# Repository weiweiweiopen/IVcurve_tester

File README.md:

# IVcurve_tester — Basic and Charging Boards

An I–V measurement circuit for dye-sensitized solar cells (DSSCs) and other low-power photovoltaic devices. Both boards use a **LOLIN S3 Mini, ADG706 load multiplexer, ADS1115 ADC, and Adafruit 4814 e-paper display**.

## Design Credits

- The basic board derives from **Marc Dusseiller's ([@dusjagr](https://github.com/dusjagr)) [IVcurve_tester](https://github.com/dusjagr/IVcurve_tester)**, including its original I–V measurement architecture, hardware, and code. This derivative adapts the carrier, GPIO assignments, and display interface.
- The charging board's **energy-harvesting, storage, power-control, and derivative PCB design was completed by Sol 6.1**.
- The original MIT copyright is retained in [LICENSE](LICENSE). Additional component-library attribution is provided in [NOTICE](NOTICE.md).

## Electrical Overview

| Function | Basic Board | Charging Board |
|---|---|---|
| System power | USB | DSSC harvesting and a controlled 5V boost supply; USB maintenance input |
| DUT connection | One DSSC, positive and negative collector pads at J1 | Same single-DSSC interface |
| I–V load selection | ADG706, 16 resistive loads | ADG706, 16 resistive loads |
| Voltage measurement | ADS1115 | ADS1115 |
| Energy harvesting | — | AEM10941 |
| Energy storage | — | Two parallel 1.5F / 5V supercapacitor packs, 3F total |
| Main power control | USB-powered operation | READY and timer logic, TPS61023 boost, TPS22917 load switch |
| Harvest/measurement switching | DUT connected to the measurement circuit | K1 relay switches the DSSC between harvesting and measurement |

## Basic Board

USB powers the MCU, ADC, and display. The DSSC is the device under test, rather than the MCU's power source.

The ADG706 selects one of 16 load resistors. The ADS1115 measures the voltage at each load point, and the firmware calculates current and power:

```text
I = V / Rpath
P = V × I
```

`Rpath` includes the selected resistor, multiplexer on-resistance, traces, and contacts. The supplied firmware uses nominal resistor values until measured path resistances and ADC calibration are entered. The ADS1115's ±4.096V gain setting describes its conversion scale; the input must still comply with its supply-dependent electrical limits.

The display interface uses the Adafruit 4814 SSD1680 panel at 250 × 122 pixels. Measurement starts from the button or the serial `SCAN` command. See the [basic firmware instructions](firmware/basic/README.md) for operation and GPIO assignments.

## Charging Board

The charging circuit harvests energy from the DSSC and stores it in **supercapacitors**. C201 and C202 are 1.5F / 5V PHB packs connected in parallel: the nominal total capacitance is **3F**, and the voltage rating remains **5V**.

```mermaid
flowchart TD
    DSSC[DSSC] --> K1[K1 relay]
    K1 -->|De-energized: harvest| AEM[AEM10941 harvester]
    AEM --> STORE[VSTORE: 3F supercapacitor bank]
    STORE --> AON[TPS7A02 always-on 3.3V]
    AON --> CONTROL[TPL5111 timer and READY logic]
    CONTROL -->|PM_READY AND TIMER_REQUEST| BOOST[TPS61023 5V boost]
    STORE --> BOOST
    BOOST --> SWITCH[TPS22917 controlled by JP201]
    SWITCH --> MCU[MCU, display, and measurement circuit]
    MCU -->|SCAN_MODE| K1
    K1 -->|Energized: measure| LOAD[ADG706 loads and ADS1115 sensing]
    MCU -->|MCU_DONE| CONTROL
```

### Harvesting and Storage

With K1 de-energized, the DSSC positive terminal connects to `HARV_P` and the AEM10941. The measurement load and ADC sensing branch are disconnected by the relay contacts.

The AEM10941 converts harvested energy into stored energy at `VSTORE`. Its configuration pins are set to `CFG=000`, corresponding to the schematic's nominal **70% Voc** MPPT setting. This hardware harvesting setting is separate from the MCU's I–V sweep and measured maximum-power-point calculation.

R280–R283 configure the AEM10941's charge and discharge thresholds. These thresholds govern when charging is limited, when stored energy is ready for use, and when the system should stop drawing from storage.

### Main Supply Control

TPS7A02 supplies the always-on 3.3V control domain. The main supply enable is:

```text
BOOST_EN = PM_READY AND TIMER_REQUEST
```

TPL5111 is configured for a nominal interval of approximately 600 seconds. The timer interval schedules a power request; actual operation also depends on the stored-energy condition. TPS61023 boosts `VSTORE` to `SOLAR_5V`, and TPS22917 connects that supply to the module's VBUS when enabled through JP201.

### Measurement and Return to Harvesting

The charging controller requires the following sequence:

1. Disable the ADG706 load before changing the relay state.
2. Assert `SCAN_MODE` to energize K1. The DSSC then connects to `LOAD_P`, while the second relay pole connects it to `SENSE_P` for the ADC. The harvesting branch is disconnected during the sweep.
3. Wait for relay contacts and the analog input to settle, then scan the load resistors and read the ADS1115.
4. Disable the load and release K1 to reconnect the DSSC to the harvester.
5. Complete the required logging/display operation and signal `MCU_DONE` through the Schmitt buffer to end the main-power interval.

`POWER_WARN_N` provides a storage-related warning input for early termination. Firmware must handle this input, relay settling, and DONE timing. The supplied basic USB firmware does not implement this autonomous charging-control sequence.

| Charging control signal | MCU GPIO | Function |
|---|---:|---|
| `SCAN_MODE` | 12 | Select harvesting or measurement through K1 |
| `MCU_DONE` | 13 | End the timer-controlled main-power interval |
| `POWER_WARN_N` | 11 | Storage/power warning input |

### USB Power and Energy Budget

Set **JP201 to OFF before connecting USB**. JP201 controls the TPS22917 load-switch path between the harvested 5V supply and module VBUS. USB is used as a maintenance supply with that path disabled.

For a supercapacitor bank, usable energy between two storage voltages is:

```text
Eusable = 0.5 × C × (Vhigh² − Vlow²)
C ≈ 3F
```

Charging time depends on DSSC output, illumination, conversion efficiency, capacitor leakage, and always-on consumption. The energy budget must include MCU activity, the relay coil, ADC operation, and display refresh. The timer's short off interval without a DONE signal must also be considered when designing the power-down and restart sequence.

## Circuit References

| | Basic Board | Charging Board |
|---|---|---|
| KiCad 10 project | [Open](hardware/basic/Marc_USB.kicad_pro) | [Open](hardware/charging/Marc_USB.kicad_pro) |
| Schematic | [PDF](hardware/basic/schematic.pdf) | [PDF](hardware/charging/schematic.pdf) |
| BOM | [CSV](hardware/basic/BOM.csv) | [CSV](hardware/charging/BOM.csv) |
| Pin/net map | [CSV](hardware/basic/checks/pin-map.csv) | [CSV](hardware/charging/checks/pin-map.csv) |
| Fabrication files | [Gerber ZIP](hardware/basic/fabrication/basic-JLCPCB.zip) | [Gerber ZIP](hardware/charging/fabrication/charging-PROTOTYPE-JLCPCB.zip) |

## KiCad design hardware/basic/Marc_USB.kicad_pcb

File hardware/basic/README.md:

# Basic USB-Powered I–V Board

The measurement architecture derives from **Marc Dusseiller's [IVcurve_tester](https://github.com/dusjagr/IVcurve_tester)**. This carrier uses a LOLIN S3 Mini, ADG706, ADS1115, and Adafruit 4814 display.

## Electrical Operation

- USB supplies the MCU, ADC, and display.
- J1 connects one DSSC through positive and negative collector pads.
- ADG706 selects one of 16 resistive loads.
- ADS1115 reads the DUT voltage. Current is calculated using the effective load-path resistance, including multiplexer and contact resistance.
- The display is an SSD1680-based, 250 × 122-pixel tricolor panel.

Enter measured load-path resistances and ADC corrections in the firmware calibration settings before relying on calibrated current or power readings. This board has no energy-harvesting or storage circuit.

## Circuit References

- [KiCad project](Marc_USB.kicad_pro)
- [Schematic PDF](schematic.pdf)
- [BOM](BOM.csv)
- [Pin/net map](checks/pin-map.csv)
- [Gerber files](fabrication/basic-JLCPCB.zip)
- [Firmware and GPIO assignments](../../firmware/basic/README.md)

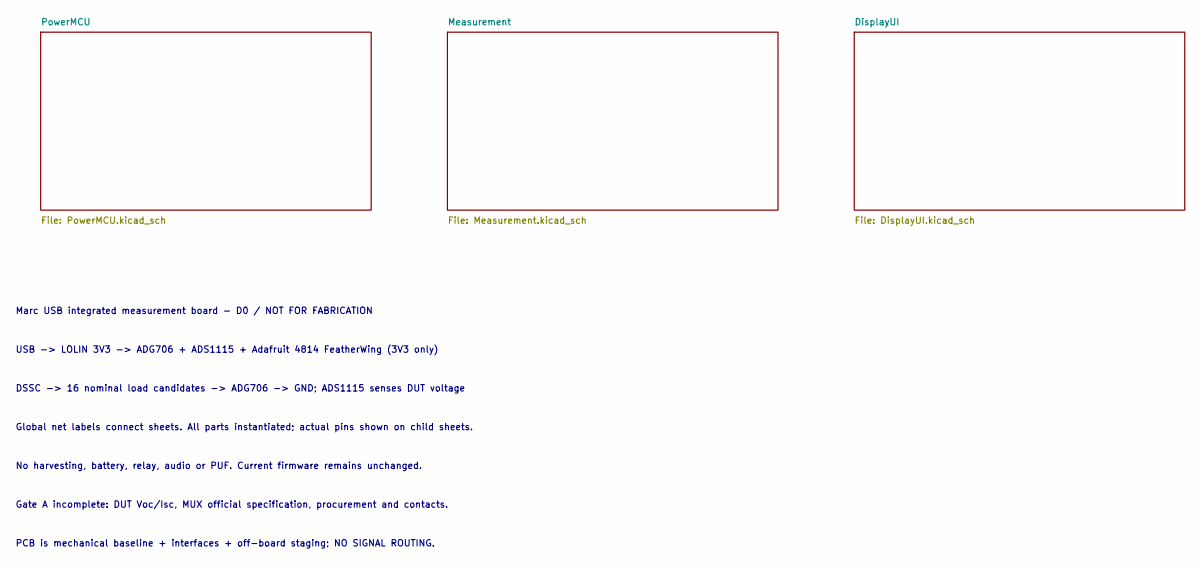
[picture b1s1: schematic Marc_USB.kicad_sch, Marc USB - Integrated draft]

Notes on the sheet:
PCB is mechanical baseline + interfaces + off-board staging; NO SIGNAL ROUTING.
Global net labels connect sheets. All parts instantiated; actual pins shown on child sheets.
Marc USB integrated measurement board - D0 / NOT FOR FABRICATION
Gate A incomplete: DUT Voc/Isc, MUX official specification, procurement and contacts.
USB -> LOLIN 3V3 -> ADG706 + ADS1115 + Adafruit 4814 FeatherWing (3V3 only)
DSSC -> 16 nominal load candidates -> ADG706 -> GND; ADS1115 senses DUT voltage
No harvesting, battery, relay, audio or PUF. Current firmware remains unchanged.

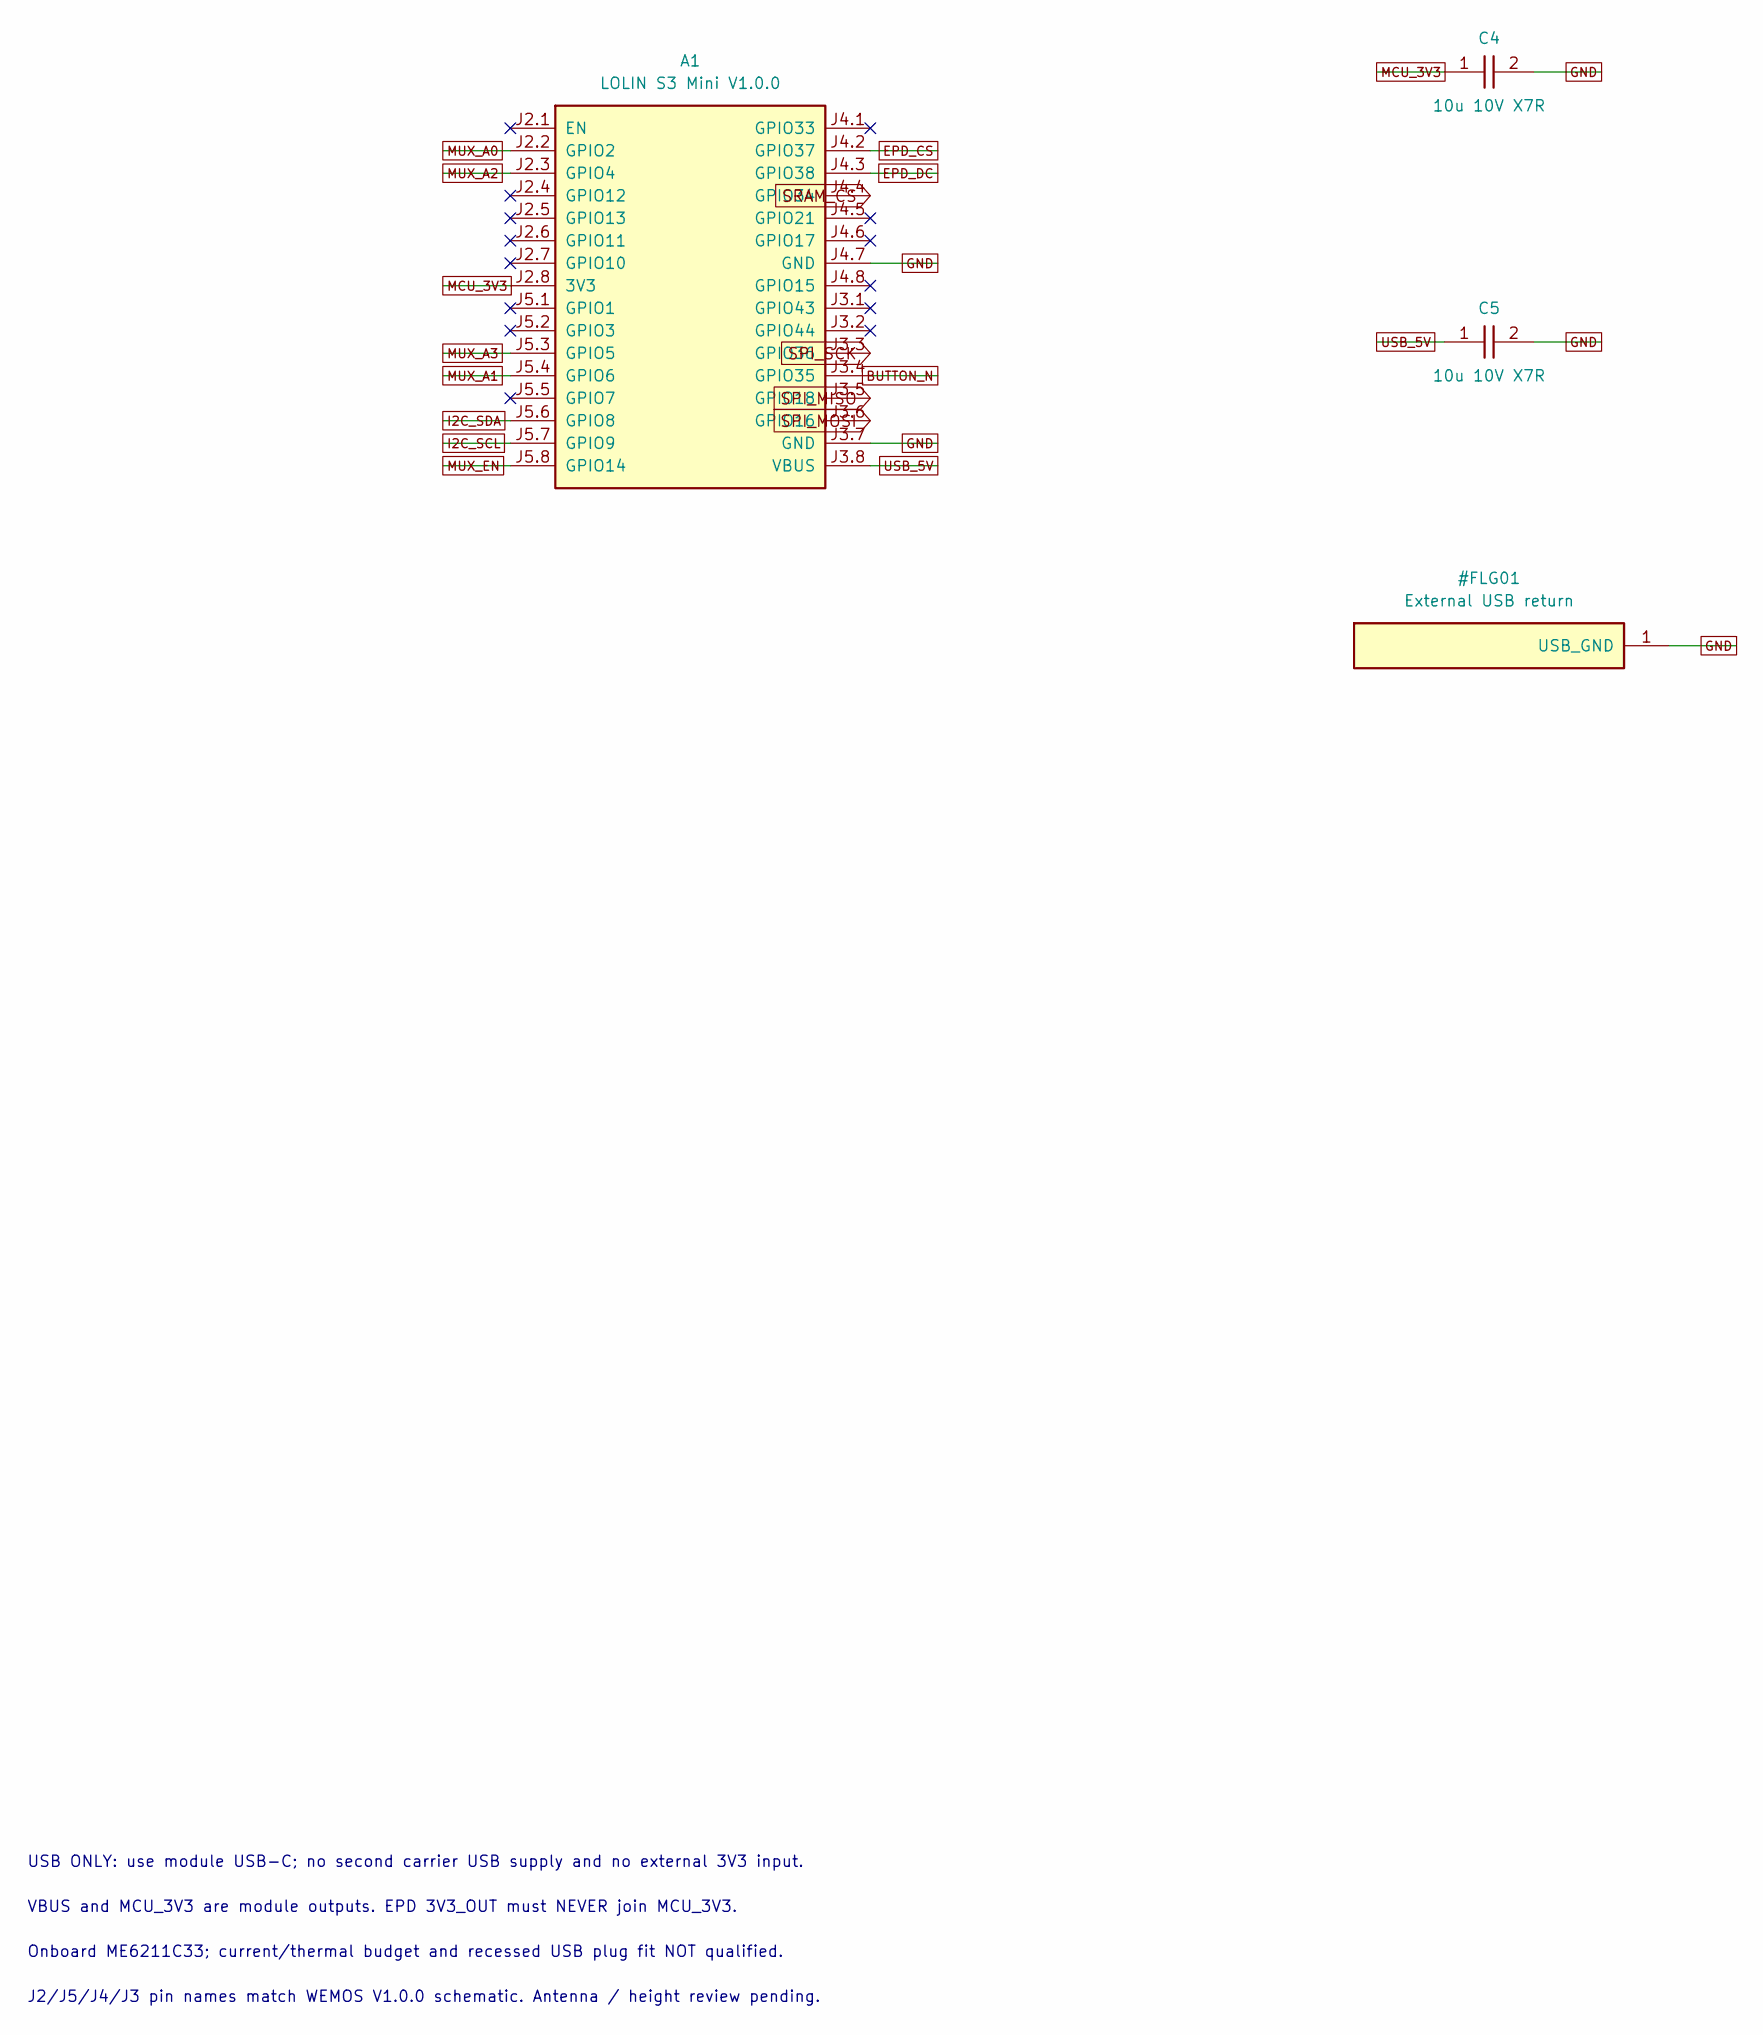
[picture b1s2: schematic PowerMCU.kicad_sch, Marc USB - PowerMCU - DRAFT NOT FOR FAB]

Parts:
A1: LOLIN S3 Mini V1.0.0; LOLIN_S3_MINI_V1; MPN LOLIN S3 MINI V1.0.0
C4, C5: 10u 10V X7R; C_0805_2012Metric

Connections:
BUTTON_N: A1.J3.4 (GPIO35); also elsewhere on the board
EPD_CS: A1.J4.2 (GPIO37); also elsewhere on the board
EPD_DC: A1.J4.3 (GPIO38); also elsewhere on the board
GND: A1.J3.7 (GND), A1.J4.7 (GND), C4.2, C5.2; also elsewhere on the board
I2C_SCL: A1.J5.7 (GPIO9); also elsewhere on the board
I2C_SDA: A1.J5.6 (GPIO8); also elsewhere on the board
MCU_3V3: A1.J2.8 (3V3), C4.1; also elsewhere on the board
MUX_A0: A1.J2.2 (GPIO2); also elsewhere on the board
MUX_A1: A1.J5.4 (GPIO6); also elsewhere on the board
MUX_A2: A1.J2.3 (GPIO4); also elsewhere on the board
MUX_A3: A1.J5.3 (GPIO5); also elsewhere on the board
MUX_EN: A1.J5.8 (GPIO14); also elsewhere on the board
SPI_MISO: A1.J3.5 (GPIO18); also elsewhere on the board
SPI_MOSI: A1.J3.6 (GPIO16); also elsewhere on the board
SPI_SCK: A1.J3.3 (GPIO36); also elsewhere on the board
SRAM_CS: A1.J4.4 (GPIO34); also elsewhere on the board
USB_5V: A1.J3.8 (VBUS), C5.1

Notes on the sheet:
USB ONLY: use module USB-C; no second carrier USB supply and no external 3V3 input.
Onboard ME6211C33; current/thermal budget and recessed USB plug fit NOT qualified.
J2/J5/J4/J3 pin names match WEMOS V1.0.0 schematic. Antenna / height review pending.
VBUS and MCU_3V3 are module outputs. EPD 3V3_OUT must NEVER join MCU_3V3.

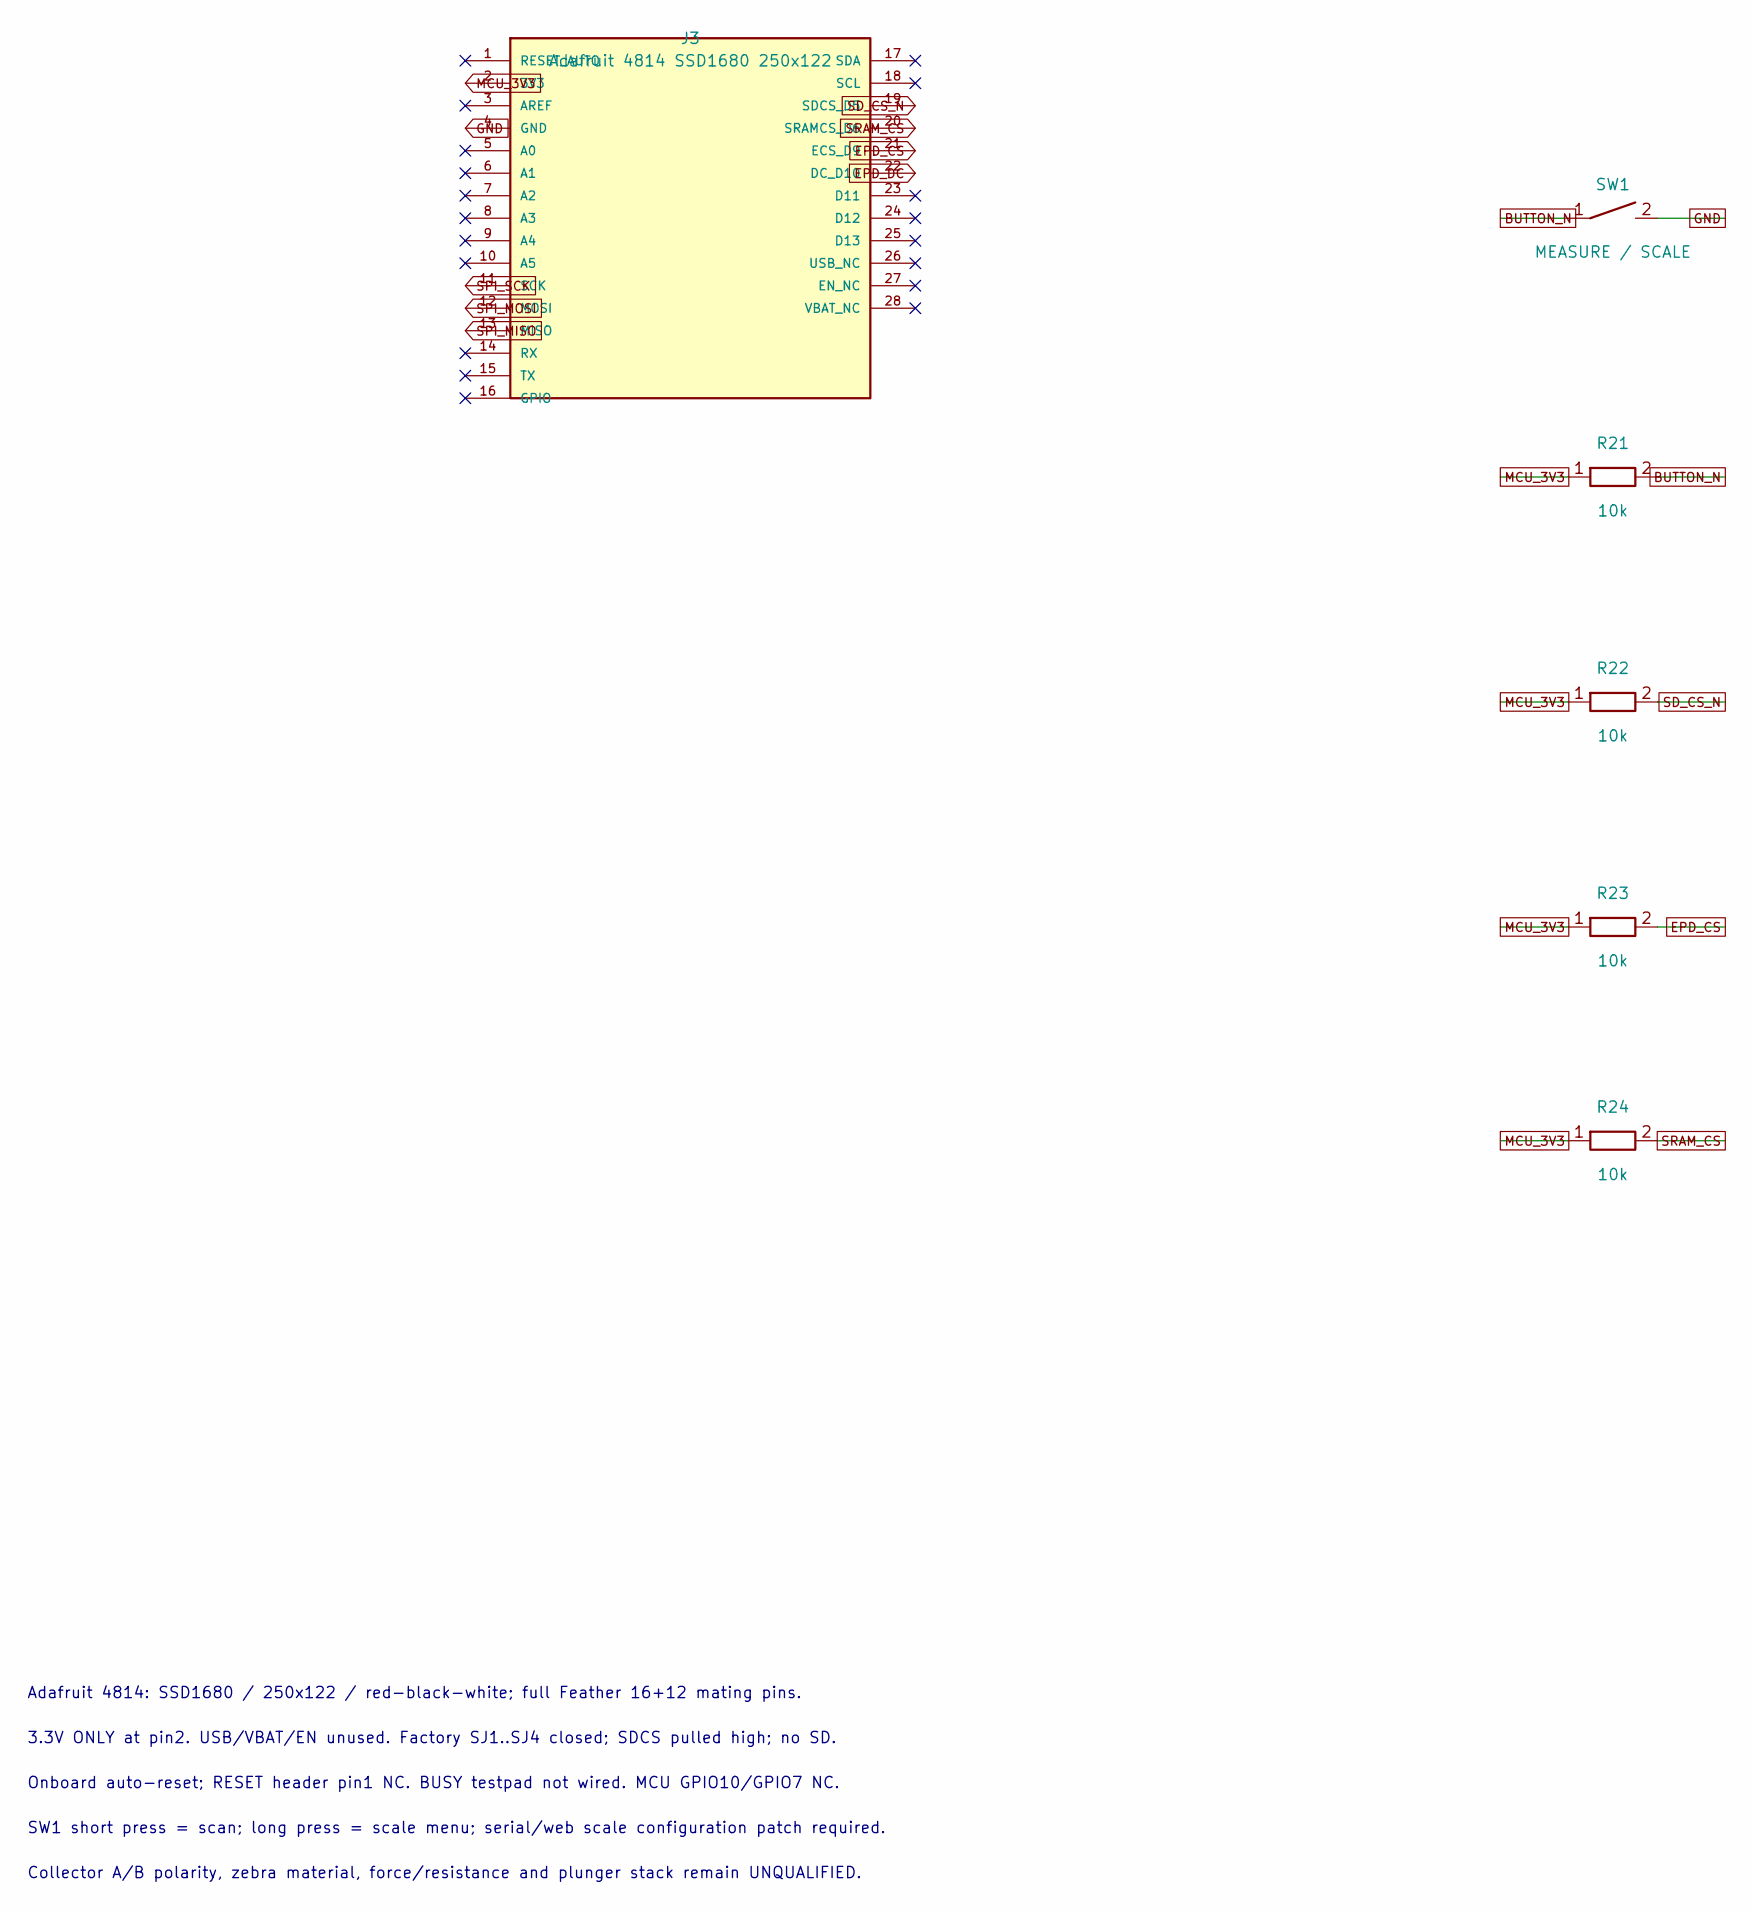
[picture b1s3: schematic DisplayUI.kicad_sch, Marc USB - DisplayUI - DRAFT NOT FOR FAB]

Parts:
J3: Adafruit 4814 SSD1680 250x122; Adafruit_4814_FeatherWing_Mating; MPN 4814
R21, R22, R23, R24: 10k; R_0603_1608Metric
SW1: MEASURE / SCALE; SW_SPST_TL3342; MPN TL3342候選

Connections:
BUTTON_N: R21.2, SW1.1; also elsewhere on the board
EPD_CS: J3.21 (ECS_D9), R23.2; also elsewhere on the board
EPD_DC: J3.22 (DC_D10); also elsewhere on the board
GND: J3.4 (GND), SW1.2; also elsewhere on the board
MCU_3V3: J3.2 (3V3), R21.1, R22.1, R23.1, R24.1; also elsewhere on the board
SD_CS_N: J3.19 (SDCS_D5), R22.2
SPI_MISO: J3.13 (MISO); also elsewhere on the board
SPI_MOSI: J3.12 (MOSI); also elsewhere on the board
SPI_SCK: J3.11 (SCK); also elsewhere on the board
SRAM_CS: J3.20 (SRAMCS_D6), R24.2; also elsewhere on the board

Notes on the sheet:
Adafruit 4814: SSD1680 / 250x122 / red-black-white; full Feather 16+12 mating pins.
3.3V ONLY at pin2. USB/VBAT/EN unused. Factory SJ1..SJ4 closed; SDCS pulled high; no SD.
Collector A/B polarity, zebra material, force/resistance and plunger stack remain UNQUALIFIED.
Onboard auto-reset; RESET header pin1 NC. BUSY testpad not wired. MCU GPIO10/GPIO7 NC.
SW1 short press = scan; long press = scale menu; serial/web scale configuration patch required.

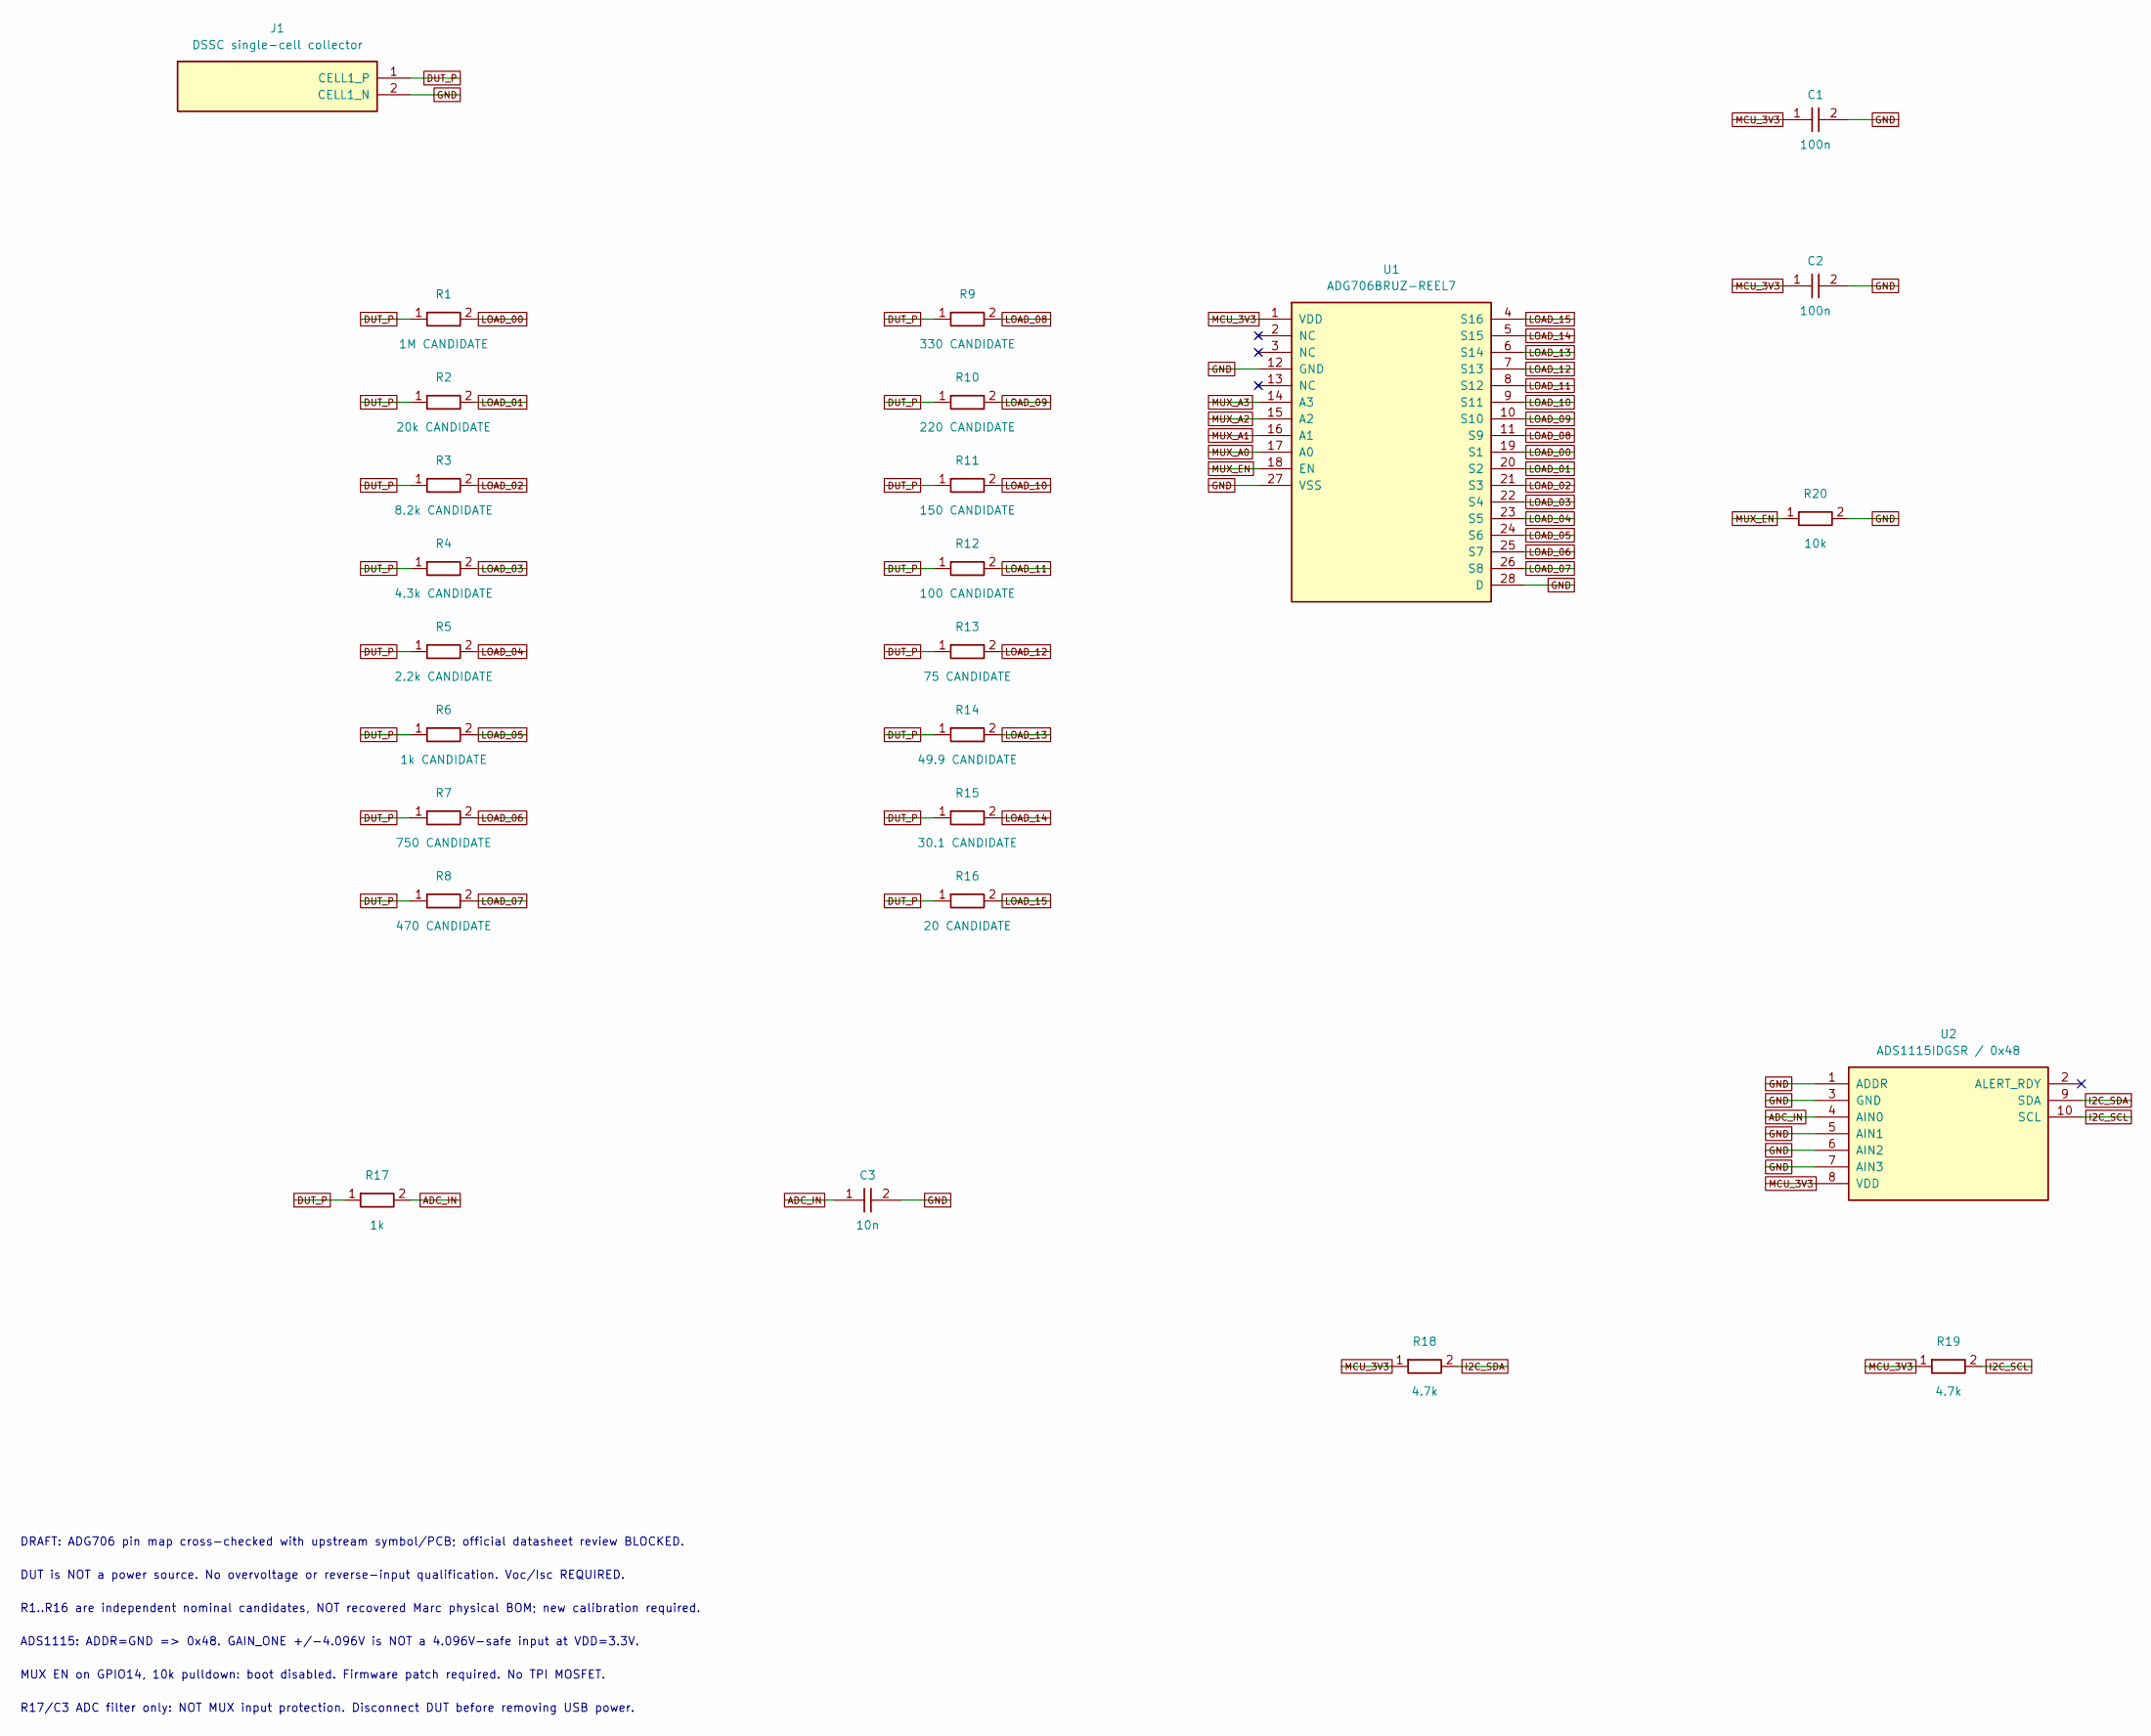
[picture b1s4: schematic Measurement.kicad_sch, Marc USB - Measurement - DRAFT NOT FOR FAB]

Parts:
C1, C2: 100n; C_0603_1608Metric
C3: 10n; C_0603_1608Metric
J1: DSSC single-cell collector; DSSC_Collector_58mm
R1: 1M CANDIDATE; R_2512_6332Metric
R2: 20k CANDIDATE; R_2512_6332Metric
R3: 8.2k CANDIDATE; R_2512_6332Metric
R4: 4.3k CANDIDATE; R_2512_6332Metric
R5: 2.2k CANDIDATE; R_2512_6332Metric
R6: 1k CANDIDATE; R_2512_6332Metric
R7: 750 CANDIDATE; R_2512_6332Metric
R8: 470 CANDIDATE; R_2512_6332Metric
R9: 330 CANDIDATE; R_2512_6332Metric
R10: 220 CANDIDATE; R_2512_6332Metric
R11: 150 CANDIDATE; R_2512_6332Metric
R12: 100 CANDIDATE; R_2512_6332Metric
R13: 75 CANDIDATE; R_2512_6332Metric
R14: 49.9 CANDIDATE; R_2512_6332Metric
R15: 30.1 CANDIDATE; R_2512_6332Metric
R16: 20 CANDIDATE; R_2512_6332Metric
R17: 1k; R_0603_1608Metric
R18, R19: 4.7k; R_0603_1608Metric
R20: 10k; R_0603_1608Metric
U1: ADG706BRUZ-REEL7; TSSOP-28_4.4x9.7mm_P0.65mm; MPN ADG706BRUZ-REEL7
U2: ADS1115IDGSR / 0x48; TSSOP-10_3x3mm_P0.5mm; MPN ADS1115IDGSR

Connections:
ADC_IN: C3.1, R17.2, U2.4 (AIN0)
DUT_P: J1.1 (CELL1_P), R1.1, R2.1, R3.1, R4.1, R5.1, R6.1, R7.1, R8.1, R9.1, R10.1, R11.1, R12.1, R13.1, R14.1, R15.1, R16.1, R17.1
GND: C1.2, C2.2, C3.2, J1.2 (CELL1_N), R20.2, U1.12 (GND), U1.27 (VSS), U1.28 (D), U2.1 (ADDR), U2.3 (GND), U2.5 (AIN1), U2.6 (AIN2), U2.7 (AIN3); also elsewhere on the board
I2C_SCL: R19.2, U2.10 (SCL); also elsewhere on the board
I2C_SDA: R18.2, U2.9 (SDA); also elsewhere on the board
LOAD_00: R1.2, U1.19 (S1)
LOAD_01: R2.2, U1.20 (S2)
LOAD_02: R3.2, U1.21 (S3)
LOAD_03: R4.2, U1.22 (S4)
LOAD_04: R5.2, U1.23 (S5)
LOAD_05: R6.2, U1.24 (S6)
LOAD_06: R7.2, U1.25 (S7)
LOAD_07: R8.2, U1.26 (S8)
LOAD_08: R9.2, U1.11 (S9)
LOAD_09: R10.2, U1.10 (S10)
LOAD_10: R11.2, U1.9 (S11)
LOAD_11: R12.2, U1.8 (S12)
LOAD_12: R13.2, U1.7 (S13)
LOAD_13: R14.2, U1.6 (S14)
LOAD_14: R15.2, U1.5 (S15)
LOAD_15: R16.2, U1.4 (S16)
MCU_3V3: C1.1, C2.1, R18.1, R19.1, U1.1 (VDD), U2.8 (VDD); also elsewhere on the board
MUX_A0: U1.17 (A0); also elsewhere on the board
MUX_A1: U1.16 (A1); also elsewhere on the board
MUX_A2: U1.15 (A2); also elsewhere on the board
MUX_A3: U1.14 (A3); also elsewhere on the board
MUX_EN: R20.1, U1.18 (EN); also elsewhere on the board

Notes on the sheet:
DRAFT: ADG706 pin map cross-checked with upstream symbol/PCB; official datasheet review BLOCKED.
DUT is NOT a power source. No overvoltage or reverse-input qualification. Voc/Isc REQUIRED.
R17/C3 ADC filter only: NOT MUX input protection. Disconnect DUT before removing USB power.
ADS1115: ADDR=GND => 0x48. GAIN_ONE +/-4.096V is NOT a 4.096V-safe input at VDD=3.3V.
MUX EN on GPIO14, 10k pulldown: boot disabled. Firmware patch required. No TPI MOSFET.
R1..R16 are independent nominal candidates, NOT recovered Marc physical BOM; new calibration required.

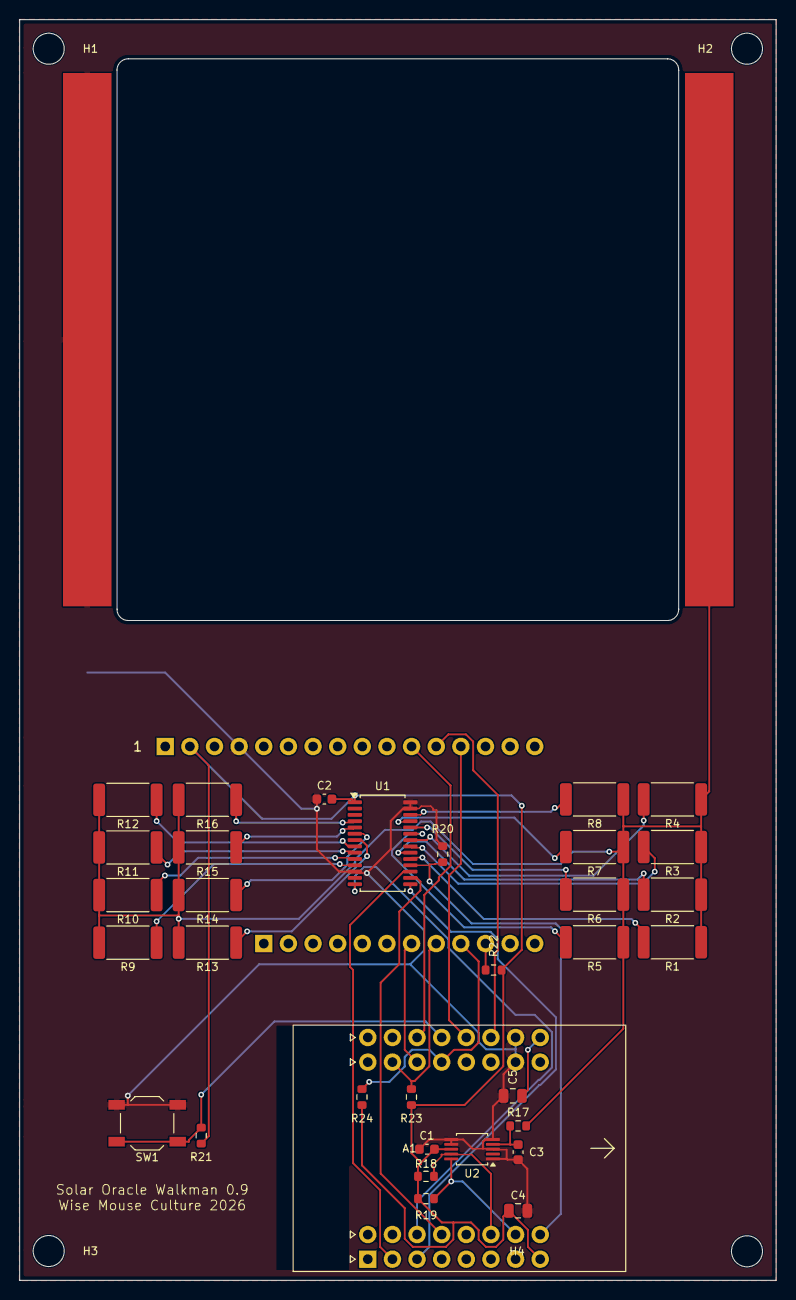
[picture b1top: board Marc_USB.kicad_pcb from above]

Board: 2 copper layers, 78.0 x 130.0 mm, 39 parts (0 on the bottom side), 36 nets.

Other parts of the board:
H1, H2, H3, H4: NPTH 3.2mm; MountingHole_3.2mm_M3

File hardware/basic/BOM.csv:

Designators,Quantity,Value,Footprint,MPN
R12,1,100 CANDIDATE,Resistor_SMD:R_2512_6332Metric,
"C1,C2",2,100n,Capacitor_SMD:C_0603_1608Metric,
"R20,R21,R22,R23,R24",5,10k,Resistor_SMD:R_0603_1608Metric,
C3,1,10n,Capacitor_SMD:C_0603_1608Metric,
"C4,C5",2,10u 10V X7R,Capacitor_SMD:C_0805_2012Metric,
R11,1,150 CANDIDATE,Resistor_SMD:R_2512_6332Metric,
R1,1,1M CANDIDATE,Resistor_SMD:R_2512_6332Metric,
R17,1,1k,Resistor_SMD:R_0603_1608Metric,
R6,1,1k CANDIDATE,Resistor_SMD:R_2512_6332Metric,
R5,1,2.2k CANDIDATE,Resistor_SMD:R_2512_6332Metric,
R16,1,20 CANDIDATE,Resistor_SMD:R_2512_6332Metric,
R2,1,20k CANDIDATE,Resistor_SMD:R_2512_6332Metric,
R10,1,220 CANDIDATE,Resistor_SMD:R_2512_6332Metric,
R15,1,30.1 CANDIDATE,Resistor_SMD:R_2512_6332Metric,
R9,1,330 CANDIDATE,Resistor_SMD:R_2512_6332Metric,
R4,1,4.3k CANDIDATE,Resistor_SMD:R_2512_6332Metric,
"R18,R19",2,4.7k,Resistor_SMD:R_0603_1608Metric,
R8,1,470 CANDIDATE,Resistor_SMD:R_2512_6332Metric,
R14,1,49.9 CANDIDATE,Resistor_SMD:R_2512_6332Metric,
R13,1,75 CANDIDATE,Resistor_SMD:R_2512_6332Metric,
R7,1,750 CANDIDATE,Resistor_SMD:R_2512_6332Metric,
R3,1,8.2k CANDIDATE,Resistor_SMD:R_2512_6332Metric,
U1,1,ADG706BRUZ-REEL7,Package_SO:TSSOP-28_4.4x9.7mm_P0.65mm,ADG706BRUZ-REEL7
U2,1,ADS1115IDGSR / 0x48,Package_SO:TSSOP-10_3x3mm_P0.5mm,ADS1115IDGSR
J3,1,Adafruit 4814 SSD1680 250x122,Marc:Adafruit_4814_FeatherWing_Mating,4814
J1,1,DSSC single-cell collector,Marc:DSSC_Collector_58mm,
A1,1,LOLIN S3 Mini V1.0.0,Marc:LOLIN_S3_MINI_V1,LOLIN S3 MINI V1.0.0
SW1,1,MEASURE / SCALE,Button_Switch_SMD:SW_SPST_TL3342,TL3342候選

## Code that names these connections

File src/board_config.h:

#ifndef BOARD_CONFIG_H
#define BOARD_CONFIG_H

// PlatformIO may select a board with a build flag. Preserve C3 as the default
// for the original tester when no environment-specific selection is supplied.
#if !defined(BOARD_ESP32S3_MINI) && !defined(BOARD_ESP32C3_SUPER_MINI)
  #define BOARD_ESP32C3_SUPER_MINI
#endif

// Choose which MUX is used
#define MUX_ADG706
//#define MUX_4051

// Choose which ADC is used
#define hasADS1115
//#define hasESPADC

// Does the system has the E-ink display?
#define hasEink

// Select exactly one physical FeatherWing panel revision.
#if !defined(EINK_ADAFRUIT_4195_GDEY0213B74) && \
    !defined(EINK_ADAFRUIT_4195_LEGACY_BN) && \
    !defined(EINK_ADAFRUIT_4814_TRICOLOR_MFGNR) && \
    !defined(EINK_ADAFRUIT_4778_TRICOLOR_Z94) && \
    !defined(EINK_ADAFRUIT_4778_TRICOLOR_Z10)
  #define EINK_ADAFRUIT_4814_TRICOLOR_MFGNR
#endif
//#define EINK_ADAFRUIT_4195_LEGACY_BN

#ifdef BOARD_ESP32S3_MINI
    #define PIN_MUX_S0      2   // MUX control pin S0
    #define PIN_MUX_S1      6   // MUX control pin S1
    #define PIN_MUX_S2      4   // MUX control pin S2
    #define PIN_MUX_S3      5   // MUX control pin S3
    #define PIN_MUX_EN      14  // ADG706 enable; active high
    #define PIN_SIG         1   // ADC input for voltage measurement
    #define PIN_POT_Y       16  // ADC input for Y-axis scaling
    #define PIN_POT_X       18  // ADC input for X-axis scaling
    #define PIN_BUTTON      35  // Digital input for mode button
    #define PIN_RGBLED      47  // RGB LED control pin

    // I2C Pin Definitions
    #define SDA_PIN 8   // Default I2C SDA for S3-Mini
    #define SCL_PIN 9   // Default I2C SCL for S3-Mini
    
    // E-ink display pins
    #define EPD_DC      38
    #define EPD_CS      37
    #define SRAM_CS     33  // FeatherWing onboard SRAM, matching the original wiring
    #define EPD_RESET   -1  // FeatherWing uses its onboard auto-reset circuit
    #define EPD_BUSY    -1

    // SPI Pins for E-ink
    #define SCLK        12
    #define MISO        13
    #define MOSI        11
#endif

#ifdef BOARD_ESP32C3_SUPER_MINI
    #define PIN_MUX_S0      0
    #define PIN_MUX_S1      1
    #define PIN_MUX_S2      5
    #define PIN_MUX_S3      10
    #define PIN_MUX_EN      20  // ADG706 enable; active high
    #define PIN_SIG         -1  // External ADS1115 is used
    #define PIN_POT_Y       -1
    #define PIN_POT_X       -1
    #define PIN_BUTTON      21
    #define PIN_RGBLED      2   // No LED fitted; keeps the legacy LED API off shared buses

    // I2C Pin Definitions
    #define SDA_PIN 8
    #define SCL_PIN 9
    
    // E-ink display pins
    #define EPD_DC      3
    #define EPD_CS      7
    #define SRAM_CS     -1  // Use the ESP32-C3 framebuffer
    #define EPD_RESET   -1
    #define EPD_BUSY    -1

    // SPI Pins for E-ink
    #define SCLK        4
    #define MISO        -1  // Display is write-only; SD and SRAM are unused
    #define MOSI        6
#endif

// Verify that a board is selected
#if !defined(BOARD_ESP32S3_MINI) && !defined(BOARD_ESP32C3_SUPER_MINI)
    #error "Please select a board by uncommenting one of the board definitions at the top of board_config.h"
#endif

#ifdef hasEink
  #if (defined(EINK_ADAFRUIT_4195_GDEY0213B74) + \
        defined(EINK_ADAFRUIT_4195_LEGACY_BN) + \
        defined(EINK_ADAFRUIT_4814_TRICOLOR_MFGNR) + \
        defined(EINK_ADAFRUIT_4778_TRICOLOR_Z94) + \
        defined(EINK_ADAFRUIT_4778_TRICOLOR_Z10)) != 1
    #error "Select exactly one supported Adafruit e-ink panel revision"
  #endif
#endif

#endif // BOARD_CONFIG_H
